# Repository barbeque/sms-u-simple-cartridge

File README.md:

# SMS-U Simple
A PCB for Sega Master System games. It's "simple" because it does not include any mapper (page switching, save RAM) logic, which means it only supports most Sega games up to 48K.

Note that this will not work on a Mark III/Japanese Master System; that system's pinout and cartridge shape is totally different.

## Current Status
In development

## Tested With
 * _Snail Maze_ ROM hack

## Bill of Materials
 * PCB
 * (E)EPROM containing your software - 27c64, up to 27c256. 27c512 may work, but only the lower half of the ROM will be accessible.
 * 0.1uF through-hole bypass capacitor

## Assembly Instructions
 1. Submit the gerbers from the Releases page to a PCB fabricator. Suggested settings: gold fingers (ENIG or ideally hard gold,) 45 degree bevel.
 2. If you didn't get edge connector beveling (45-degree fingers) from your PCB fabricator, it may make sense to do the beveling yourself with a sanding block.
 3. Place components onto board. If you are socketing your ROM, the socket may add too much additional height and keep a stock case from fitting.
 4. If you are using a 27c64 for your EPROM (rare,) cut the A14 jumper in the top right of the board and connect the +5V jumper instead. Verify with a multimeter.

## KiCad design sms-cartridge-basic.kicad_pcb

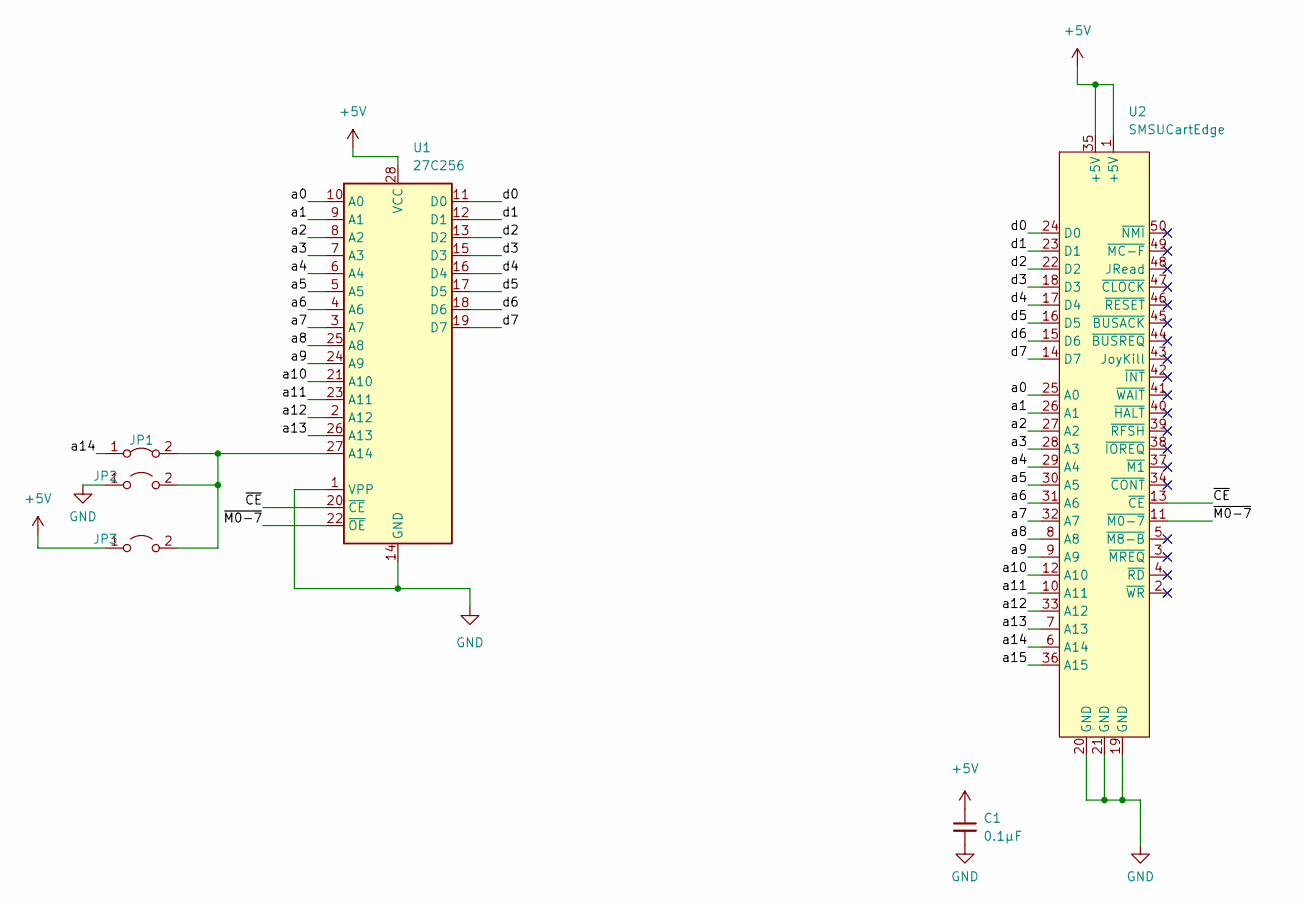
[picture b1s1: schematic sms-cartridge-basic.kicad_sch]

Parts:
C1: 0.1µF; C_Disc_D3.8mm_W2.6mm_P2.50mm
JP1: Jumper_2_Bridged; SolderJumper-2_P1.3mm_Bridged_RoundedPad1.0x1.5mm
JP2, JP3: Jumper_2_Open; SolderJumper-2_P1.3mm_Open_RoundedPad1.0x1.5mm
U1: 27C256; DIP-28_W15.24mm
U2: SMSUCartEdge; SMS_Cartridge

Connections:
+5V: C1.1, JP3.1 (A), U1.28 (VCC), U2.1 (+5V), U2.35 (+5V)
/a0: U1.10 (A0), U2.25 (A0)
/a1: U1.9 (A1), U2.26 (A1)
/a2: U1.8 (A2), U2.27 (A2)
/a3: U1.7 (A3), U2.28 (A3)
/a4: U1.6 (A4), U2.29 (A4)
/a5: U1.5 (A5), U2.30 (A5)
/a6: U1.4 (A6), U2.31 (A6)
/a7: U1.3 (A7), U2.32 (A7)
/a8: U1.25 (A8), U2.8 (A8)
/a9: U1.24 (A9), U2.9 (A9)
/a10: U1.21 (A10), U2.12 (A10)
/a11: U1.23 (A11), U2.10 (A11)
/a12: U1.2 (A12), U2.33 (A12)
/a13: U1.26 (A13), U2.7 (A13)
/a14: JP1.1 (A), U2.6 (A14)
/a15: U2.36 (A15)
/d0: U1.11 (D0), U2.24 (D0)
/d1: U1.12 (D1), U2.23 (D1)
/d2: U1.13 (D2), U2.22 (D2)
/d3: U1.15 (D3), U2.18 (D3)
/d4: U1.16 (D4), U2.17 (D4)
/d5: U1.17 (D5), U2.16 (D5)
/d6: U1.18 (D6), U2.15 (D6)
/d7: U1.19 (D7), U2.14 (D7)
/~CE: U1.20 (~CE), U2.13 (~CE)
/~M0-7: U1.22 (~OE), U2.11 (~M0-7)
GND: C1.2, JP2.1 (A), U1.1 (VPP), U1.14 (GND), U2.19 (GND), U2.20 (GND), U2.21 (GND)
unnamed: JP1.2 (B), JP2.2 (B), JP3.2 (B), U1.27 (A14)

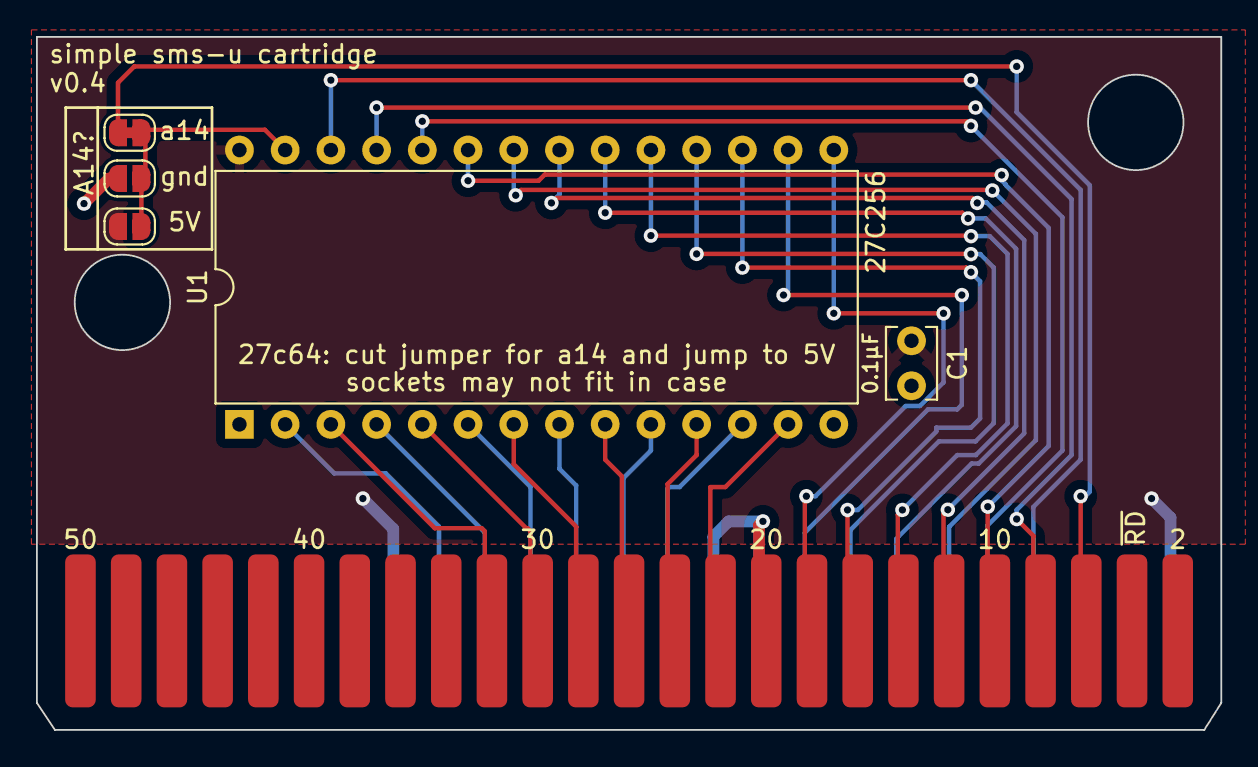
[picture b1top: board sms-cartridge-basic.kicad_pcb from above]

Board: 2 copper layers, 65.8 x 38.5 mm, 6 parts (0 on the bottom side), 28 nets.

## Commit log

2023-01-05 Basic outline
2023-01-05 Edge connector symbol, basic schematic
2023-01-05 v0.1
2023-01-20 Wider (0.8mm measurement error), wider teeth
2023-01-20 Readme
2023-01-20 Fab instructions
2023-01-20 Bodge to M0-7
2023-01-31 Prepare for v3
2023-02-07 27c64 support
2023-02-07 Update schematic
2025-03-04 Upgrade to KiCad 9
